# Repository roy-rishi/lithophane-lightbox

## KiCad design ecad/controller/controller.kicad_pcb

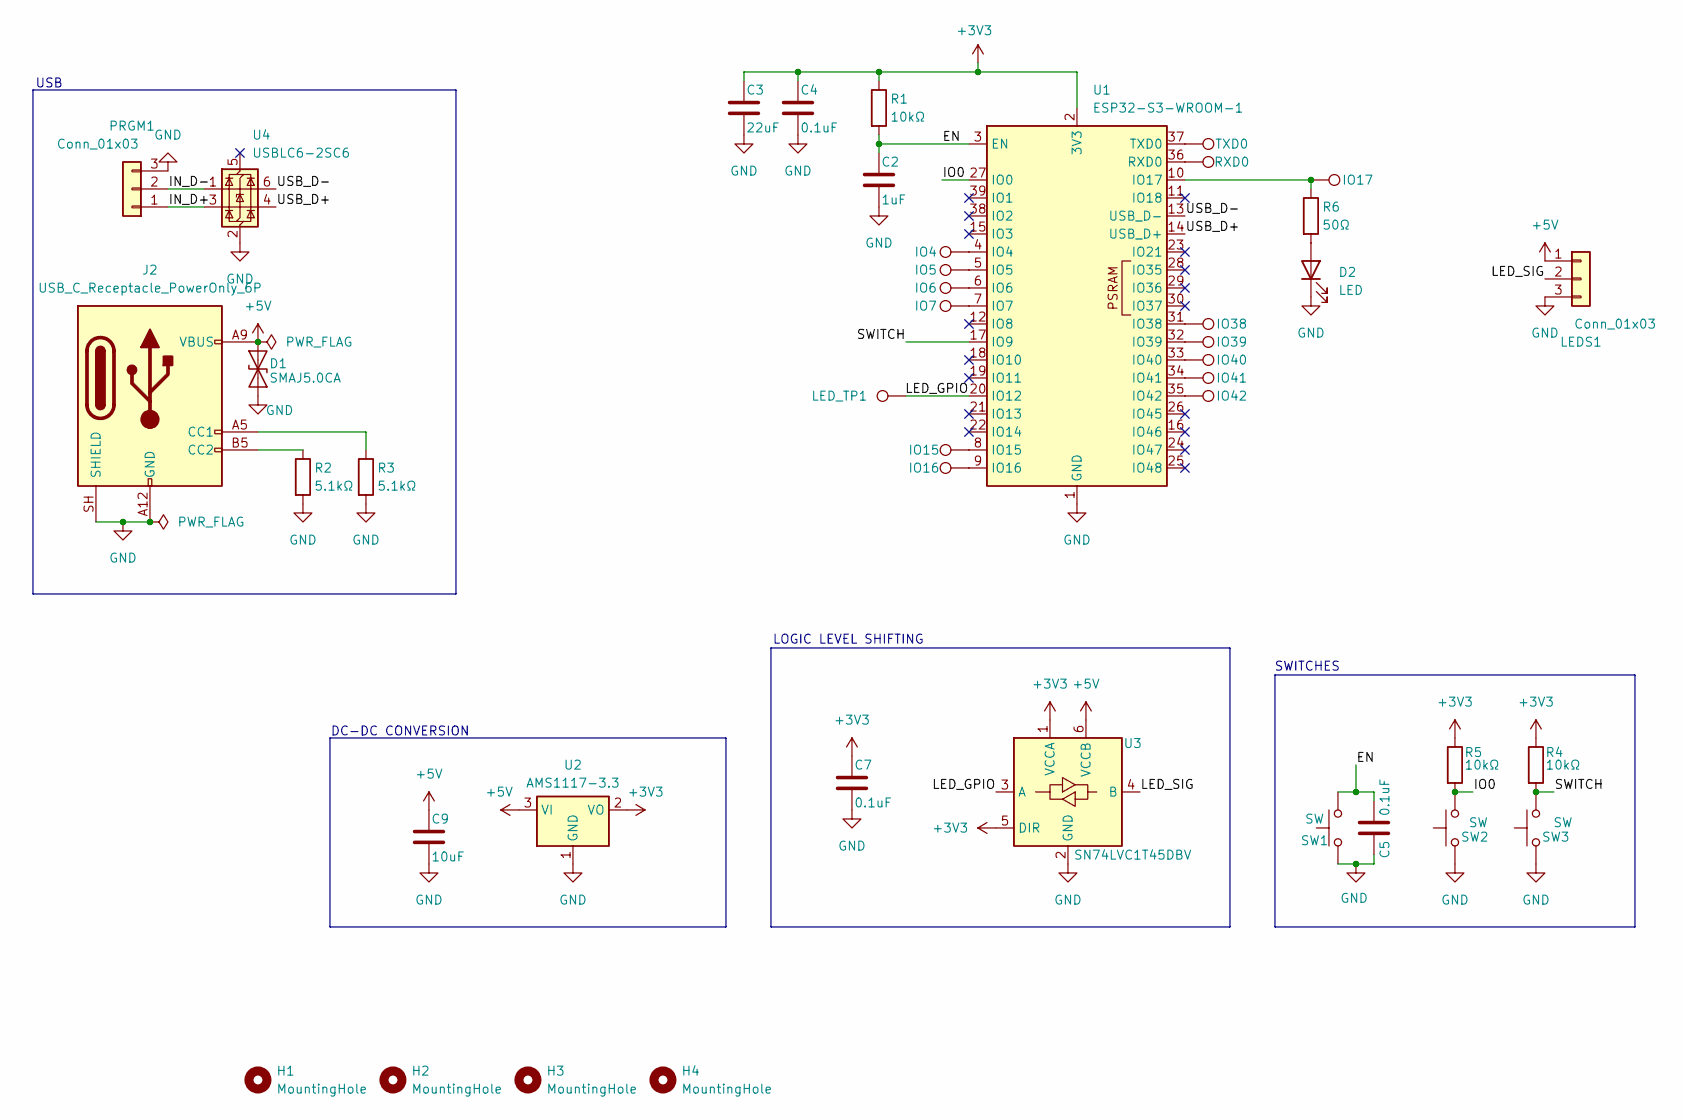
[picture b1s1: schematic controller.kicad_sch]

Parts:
C2: 1uF; C_0805_2012Metric; MPN CL21B105KBFNNNE; LCSC# C28323
C3: 22uF; C_0805_2012Metric; MPN GRM21BR61E226ME44L; LCSC# C86816
C4, C5, C7: 0.1uF; C_0805_2012Metric; MPN CL21B104KBCNNNC; LCSC# C1711
C9: 10uF; C_0805_2012Metric; MPN CL21A106KAYNNNE; LCSC# C15850
D1: SMAJ5.0CA; D_SMA; MPN SMAJ5.0CA; LCSC# C83324
D2: LED; LED_0805_2012Metric_Pad1.15x1.40mm_HandSolder; MPN XL-2012SURC; LCSC# C965812
H1, H2, H3, H4: MountingHole; MountingHole_3.2mm_M3_DIN965_Pad_TopOnly
IO4, IO5, IO6, IO7, IO15, IO16, IO17, IO38, IO39, IO40, IO41, IO42: TestPoint; TestPoint_Pad_D1.5mm
J2: USB_C_Receptacle_PowerOnly_6P; usb-c-vertical-smd; MPN TYPE-C 6PLTH6.8-DJ; LCSC# C5156600
LEDS1: Conn_01x03; JST_XH_B3B-XH-AM_1x03_P2.50mm_Vertical; MPN B3B-XH-A(LF)(SN); LCSC# C144394
LED_TP1: TestPoint; TestPoint_Pad_D1.5mm
PRGM1: Conn_01x03; PinHeader_1x03_P2.54mm_Vertical; MPN HX PH254-01-03-Z-L11.5 pcb pin header; LCSC# C52016391
R1, R4, R5: 10kΩ; R_0805_2012Metric; MPN FRC0805F1002TS; LCSC# C2907219
R2, R3: 5.1kΩ; R_0805_2012Metric; MPN RC0805FR-075K1L; LCSC# C84375
R6: 50Ω; R_0805_2012Metric; MPN ARG05FTC0500; LCSC# C2828866
RXD0: TestPoint; TestPoint_Pad_D1.5mm
SW1, SW2, SW3: SW; SW_SPST_TS-1088-xR020; MPN TS-1088-AR02016; LCSC# C720477
TXD0: TestPoint; TestPoint_Pad_D1.5mm
U1: ESP32-S3-WROOM-1; MPN ESP32-S3-WROOM-1-N16R8; LCSC# C2913202
U2: AMS1117-3.3; SOT-223-3_TabPin2; MPN AMS1117-3.3; LCSC# C6186
U3: SN74LVC1T45DBV; SOT-23-6_Handsoldering; MPN SN74LVC1T45DBVR; LCSC# C7843
U4: USBLC6-2SC6; SOT-23-6_Handsoldering; MPN USBLC6-2SC6; LCSC# C7519

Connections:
+3V3: C3.1, C4.1, C7.1, R1.1, R4.1, R5.1, U1.2 (3V3), U2.2 (VO), U3.1 (VCCA), U3.5 (DIR)
+5V: C9.1, D1.2 (A2), J2.A9 (VBUS), J2.B9 (VBUS), LEDS1.1, U2.3 (VI), U3.6 (VCCB)
/EN: C2.1, C5.1, R1.2, SW1.2, U1.3 (EN)
/IN_D+: PRGM1.1, U4.3 (I/O2)
/IN_D-: PRGM1.2, U4.1 (I/O1)
/IO0: R5.2, SW2.2, U1.27 (IO0)
/LED_GPIO: LED_TP1.1 (1_1), U1.20 (IO12), U3.3 (A)
/LED_SIG: LEDS1.2, U3.4 (B)
/SWITCH: R4.2, SW3.2, U1.17 (IO9)
/USB_D+: U1.14 (USB_D+), U4.4 (I/O2)
/USB_D-: U1.13 (USB_D-), U4.6 (I/O1)
GND: C2.2, C3.2, C4.2, C5.2, C7.2, C9.2, D1.1 (A1), D2.1 (K), J2.A12 (GND), J2.B12 (GND), J2.SH (SHIELD), LEDS1.3, PRGM1.3, R2.2, R3.2, SW1.1, SW2.1, SW3.1, U1.1 (GND), U1.40 (GND), U1.41 (GND), U2.1 (GND), U3.2 (GND), U4.2 (GND)
unnamed: D2.2 (A), R6.2
unnamed: J2.A5 (CC1), R3.1
unnamed: J2.B5 (CC2), R2.1
unnamed: IO4.1 (1_1), U1.4 (IO4)
unnamed: IO5.1 (1_1), U1.5 (IO5)
unnamed: IO6.1 (1_1), U1.6 (IO6)
unnamed: IO7.1 (1_1), U1.7 (IO7)
unnamed: IO15.1 (1_1), U1.8 (IO15)
unnamed: IO16.1 (1_1), U1.9 (IO16)
unnamed: IO17.1 (1_1), R6.1, U1.10 (IO17)
unnamed: IO38.1 (1_1), U1.31 (IO38)
unnamed: IO39.1 (1_1), U1.32 (IO39)
unnamed: IO40.1 (1_1), U1.33 (IO40)
unnamed: IO41.1 (1_1), U1.34 (IO41)
unnamed: IO42.1 (1_1), U1.35 (IO42)
unnamed: RXD0.1 (1_1), U1.36 (RXD0)
unnamed: TXD0.1 (1_1), U1.37 (TXD0)

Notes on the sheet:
SWITCHES
DC-DC CONVERSION
USB
LOGIC LEVEL SHIFTING

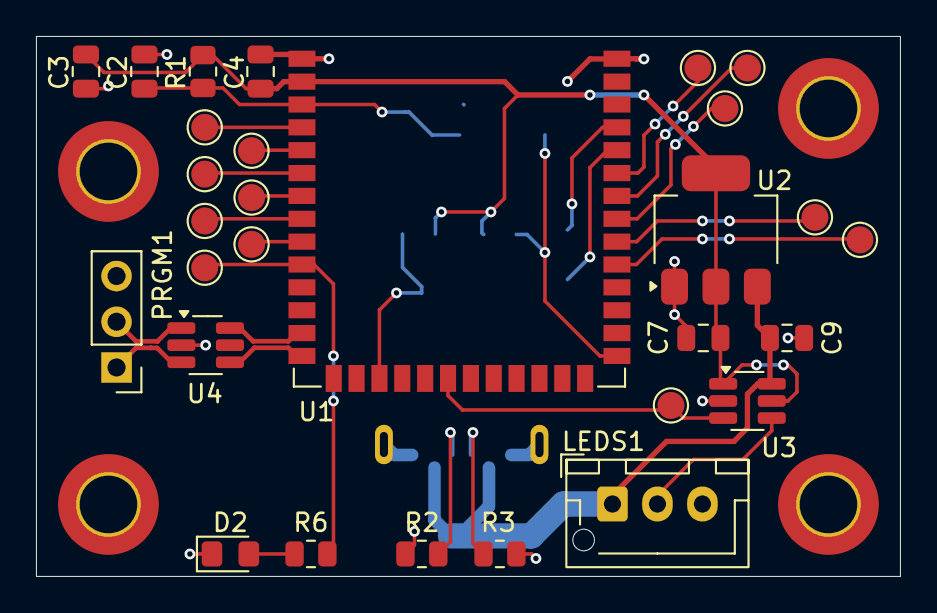
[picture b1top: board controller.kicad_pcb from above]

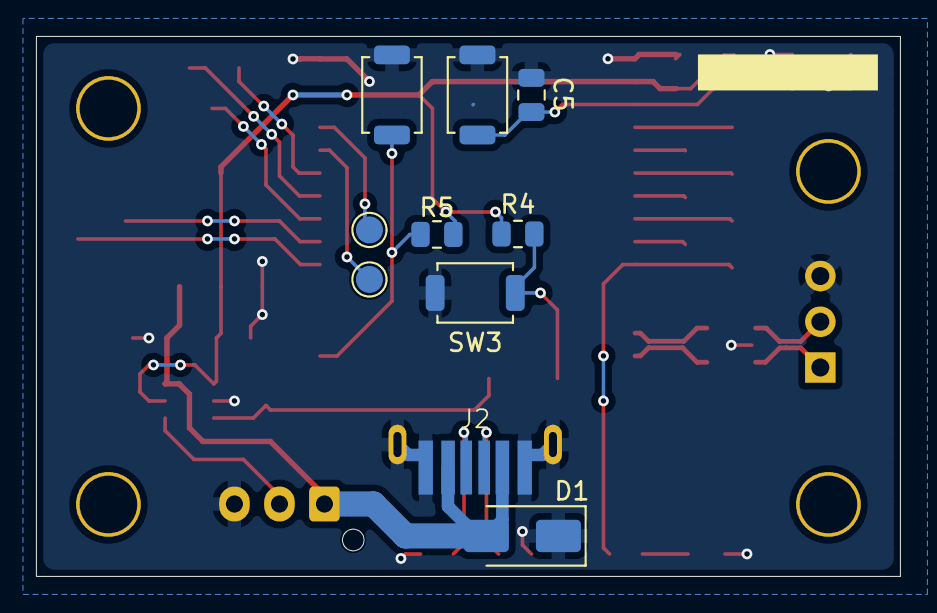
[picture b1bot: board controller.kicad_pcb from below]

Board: 2 copper layers, 48.0 x 30.0 mm, 43 parts (10 on the bottom side), 29 nets.

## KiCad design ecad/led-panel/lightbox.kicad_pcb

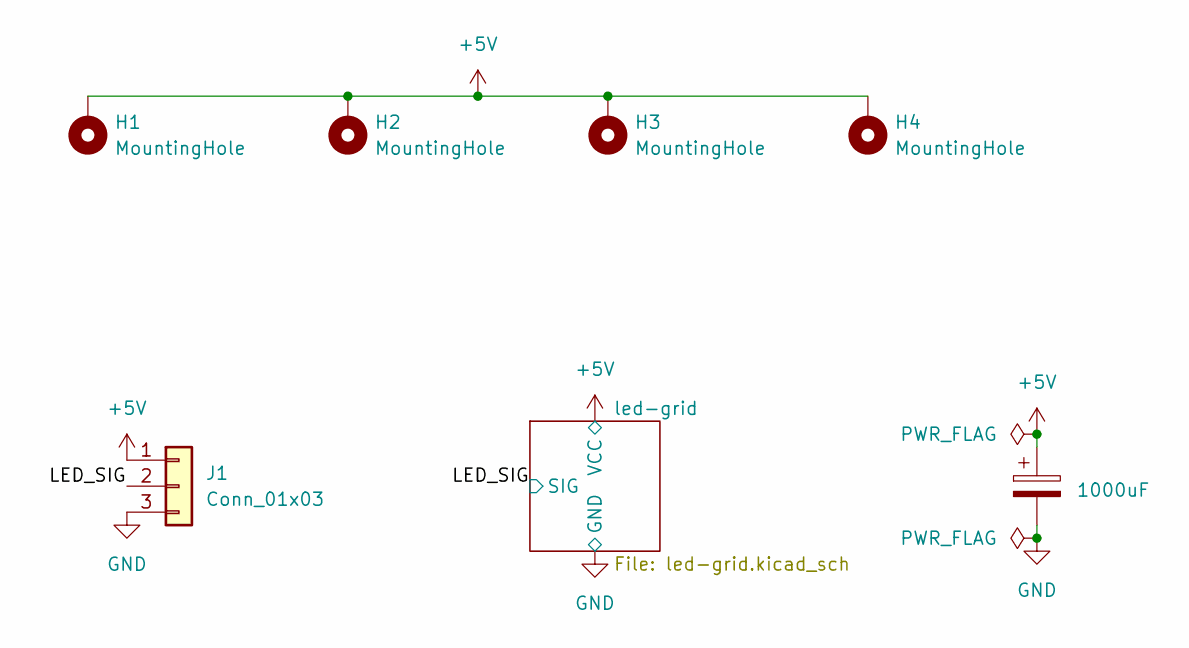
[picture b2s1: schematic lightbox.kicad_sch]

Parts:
C1: 1000uF; C_Elec_10x10.2; MPN RVT1C102M1010; LCSC# C72470
H1, H2, H3, H4: MountingHole; MountingHole_4.3mm_M4_ISO7380_Pad_TopOnly
J1: Conn_01x03; JST_XH_B3B-XH-AM_1x03_P2.50mm_Vertical; MPN B3B-XH-A(LF)(SN); LCSC# C144394

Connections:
+5V: C1.1, H1.1 (1_1), H2.1 (1_1), H3.1 (1_1), H4.1 (1_1), J1.1; also elsewhere on the board
/LED_SIG: J1.2; also elsewhere on the board
GND: C1.2, J1.3; also elsewhere on the board

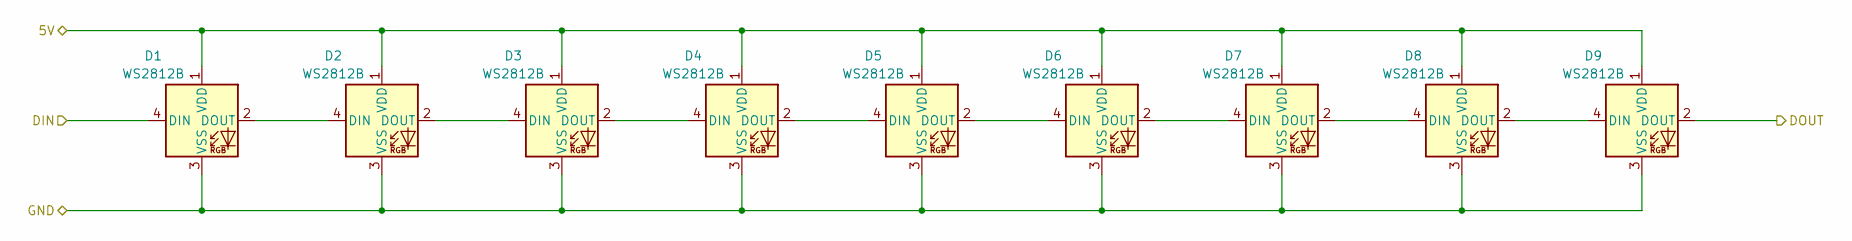
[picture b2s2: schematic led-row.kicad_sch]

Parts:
D1, D2, D3, D4, D5, D6, D7, D8, D9: WS2812B; LED_WS2812B_PLCC4_5.0x5.0mm_P3.2mm; MPN WS2812B-V5/W; LCSC# C2874885

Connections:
+5V: D1.1 (VDD), D2.1 (VDD), D3.1 (VDD), D4.1 (VDD), D5.1 (VDD), D6.1 (VDD), D7.1 (VDD), D8.1 (VDD), D9.1 (VDD); also elsewhere on the board
/LED_SIG: D1.4 (DIN); also elsewhere on the board
/led-grid/led-row/DOUT: D9.2 (DOUT); also elsewhere on the board
GND: D1.3 (VSS), D2.3 (VSS), D3.3 (VSS), D4.3 (VSS), D5.3 (VSS), D6.3 (VSS), D7.3 (VSS), D8.3 (VSS), D9.3 (VSS); also elsewhere on the board
unnamed: D1.2 (DOUT), D2.4 (DIN)
unnamed: D2.2 (DOUT), D3.4 (DIN)
unnamed: D3.2 (DOUT), D4.4 (DIN)
unnamed: D4.2 (DOUT), D5.4 (DIN)
unnamed: D5.2 (DOUT), D6.4 (DIN)
unnamed: D6.2 (DOUT), D7.4 (DIN)
unnamed: D7.2 (DOUT), D8.4 (DIN)
unnamed: D8.2 (DOUT), D9.4 (DIN)

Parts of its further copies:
D10, D11, D12, D13, D14, D15, D16, D17, D18, D19, D20, D21, D22, D23, D24, D25, D26, D27, D28, D29, D30, D31, D32, D33, D34, D35, D36, D37, D38, D39, D40, D41, D42, D43, D44, D45, D46, D47, D48, D49, D50, D51, D52, D53, D54: WS2812B; LED_WS2812B_PLCC4_5.0x5.0mm_P3.2mm; MPN WS2812B-V5/W; LCSC# C2874885

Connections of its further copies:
+5V: D10.1 (VDD), D11.1 (VDD), D12.1 (VDD), D13.1 (VDD), D14.1 (VDD), D15.1 (VDD), D16.1 (VDD), D17.1 (VDD), D18.1 (VDD), D19.1 (VDD), D20.1 (VDD), D21.1 (VDD), D22.1 (VDD), D23.1 (VDD), D24.1 (VDD), D25.1 (VDD), D26.1 (VDD), D27.1 (VDD), D28.1 (VDD), D29.1 (VDD), D30.1 (VDD), D31.1 (VDD), D32.1 (VDD), D33.1 (VDD), D34.1 (VDD), D35.1 (VDD), D36.1 (VDD), D37.1 (VDD), D38.1 (VDD), D39.1 (VDD), D40.1 (VDD), D41.1 (VDD), D42.1 (VDD), D43.1 (VDD), D44.1 (VDD), D45.1 (VDD), D46.1 (VDD), D47.1 (VDD), D48.1 (VDD), D49.1 (VDD), D50.1 (VDD), D51.1 (VDD), D52.1 (VDD), D53.1 (VDD), D54.1 (VDD); also elsewhere on the board
/led-grid/led-row1/DOUT: D18.2 (DOUT), D19.4 (DIN)
/led-grid/led-row2/DOUT: D27.2 (DOUT), D28.4 (DIN)
/led-grid/led-row3/DOUT: D36.2 (DOUT), D37.4 (DIN)
/led-grid/led-row4/DOUT: D45.2 (DOUT), D46.4 (DIN)
/led-grid/led-row5/DOUT: D54.2 (DOUT)
/led-grid/led-row/DOUT: D10.4 (DIN); also elsewhere on the board
GND: D10.3 (VSS), D11.3 (VSS), D12.3 (VSS), D13.3 (VSS), D14.3 (VSS), D15.3 (VSS), D16.3 (VSS), D17.3 (VSS), D18.3 (VSS), D19.3 (VSS), D20.3 (VSS), D21.3 (VSS), D22.3 (VSS), D23.3 (VSS), D24.3 (VSS), D25.3 (VSS), D26.3 (VSS), D27.3 (VSS), D28.3 (VSS), D29.3 (VSS), D30.3 (VSS), D31.3 (VSS), D32.3 (VSS), D33.3 (VSS), D34.3 (VSS), D35.3 (VSS), D36.3 (VSS), D37.3 (VSS), D38.3 (VSS), D39.3 (VSS), D40.3 (VSS), D41.3 (VSS), D42.3 (VSS), D43.3 (VSS), D44.3 (VSS), D45.3 (VSS), D46.3 (VSS), D47.3 (VSS), D48.3 (VSS), D49.3 (VSS), D50.3 (VSS), D51.3 (VSS), D52.3 (VSS), D53.3 (VSS), D54.3 (VSS); also elsewhere on the board
unnamed: D10.2 (DOUT), D11.4 (DIN)
unnamed: D11.2 (DOUT), D12.4 (DIN)
unnamed: D12.2 (DOUT), D13.4 (DIN)
unnamed: D13.2 (DOUT), D14.4 (DIN)
unnamed: D14.2 (DOUT), D15.4 (DIN)
unnamed: D15.2 (DOUT), D16.4 (DIN)
unnamed: D16.2 (DOUT), D17.4 (DIN)
unnamed: D17.2 (DOUT), D18.4 (DIN)
unnamed: D19.2 (DOUT), D20.4 (DIN)
unnamed: D20.2 (DOUT), D21.4 (DIN)
unnamed: D21.2 (DOUT), D22.4 (DIN)
unnamed: D22.2 (DOUT), D23.4 (DIN)
unnamed: D23.2 (DOUT), D24.4 (DIN)
unnamed: D24.2 (DOUT), D25.4 (DIN)
unnamed: D25.2 (DOUT), D26.4 (DIN)
unnamed: D26.2 (DOUT), D27.4 (DIN)
unnamed: D28.2 (DOUT), D29.4 (DIN)
unnamed: D29.2 (DOUT), D30.4 (DIN)
unnamed: D30.2 (DOUT), D31.4 (DIN)
unnamed: D31.2 (DOUT), D32.4 (DIN)
unnamed: D32.2 (DOUT), D33.4 (DIN)
unnamed: D33.2 (DOUT), D34.4 (DIN)
unnamed: D34.2 (DOUT), D35.4 (DIN)
unnamed: D35.2 (DOUT), D36.4 (DIN)
unnamed: D37.2 (DOUT), D38.4 (DIN)
unnamed: D38.2 (DOUT), D39.4 (DIN)
unnamed: D39.2 (DOUT), D40.4 (DIN)
unnamed: D40.2 (DOUT), D41.4 (DIN)
unnamed: D41.2 (DOUT), D42.4 (DIN)
unnamed: D42.2 (DOUT), D43.4 (DIN)
unnamed: D43.2 (DOUT), D44.4 (DIN)
unnamed: D44.2 (DOUT), D45.4 (DIN)
unnamed: D46.2 (DOUT), D47.4 (DIN)
unnamed: D47.2 (DOUT), D48.4 (DIN)
unnamed: D48.2 (DOUT), D49.4 (DIN)
unnamed: D49.2 (DOUT), D50.4 (DIN)
unnamed: D50.2 (DOUT), D51.4 (DIN)
unnamed: D51.2 (DOUT), D52.4 (DIN)
unnamed: D52.2 (DOUT), D53.4 (DIN)
unnamed: D53.2 (DOUT), D54.4 (DIN)

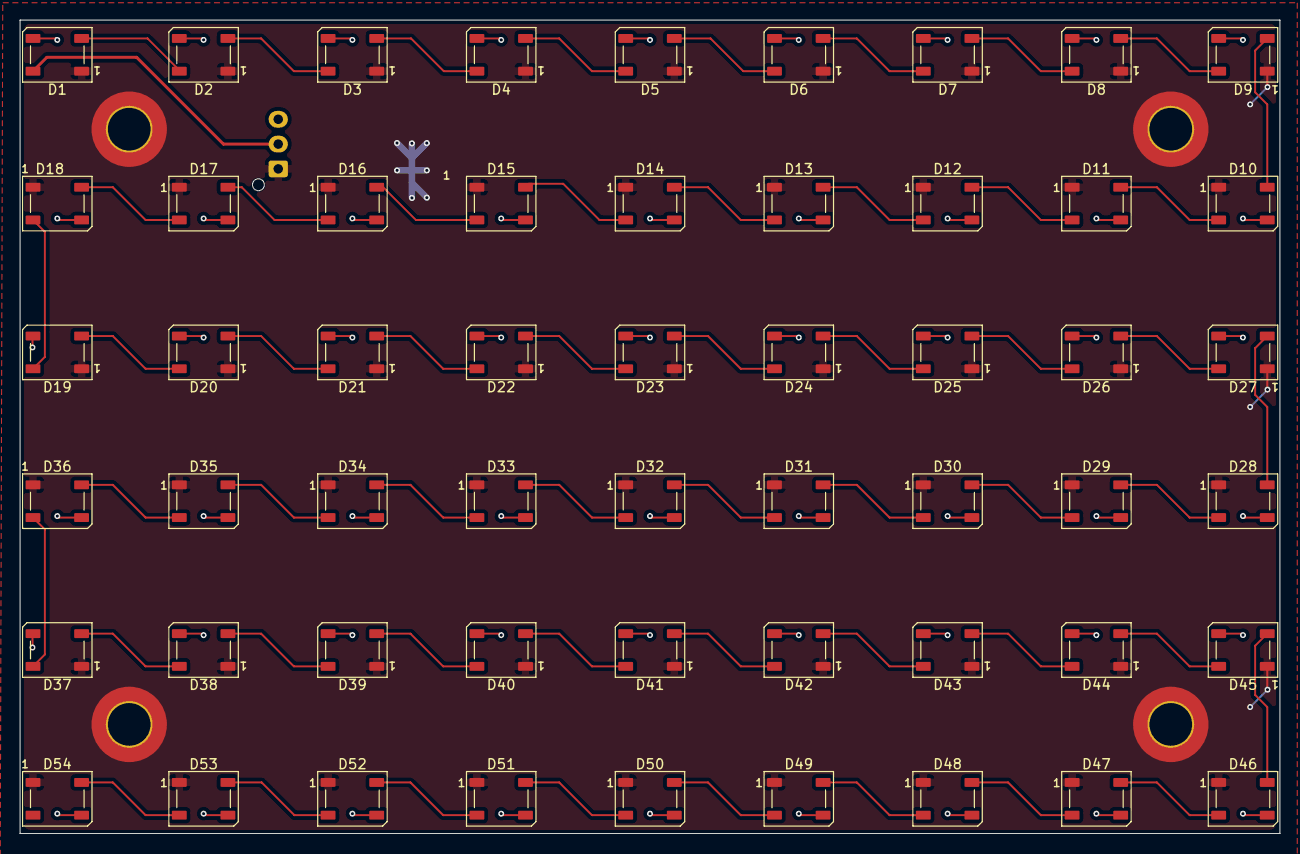
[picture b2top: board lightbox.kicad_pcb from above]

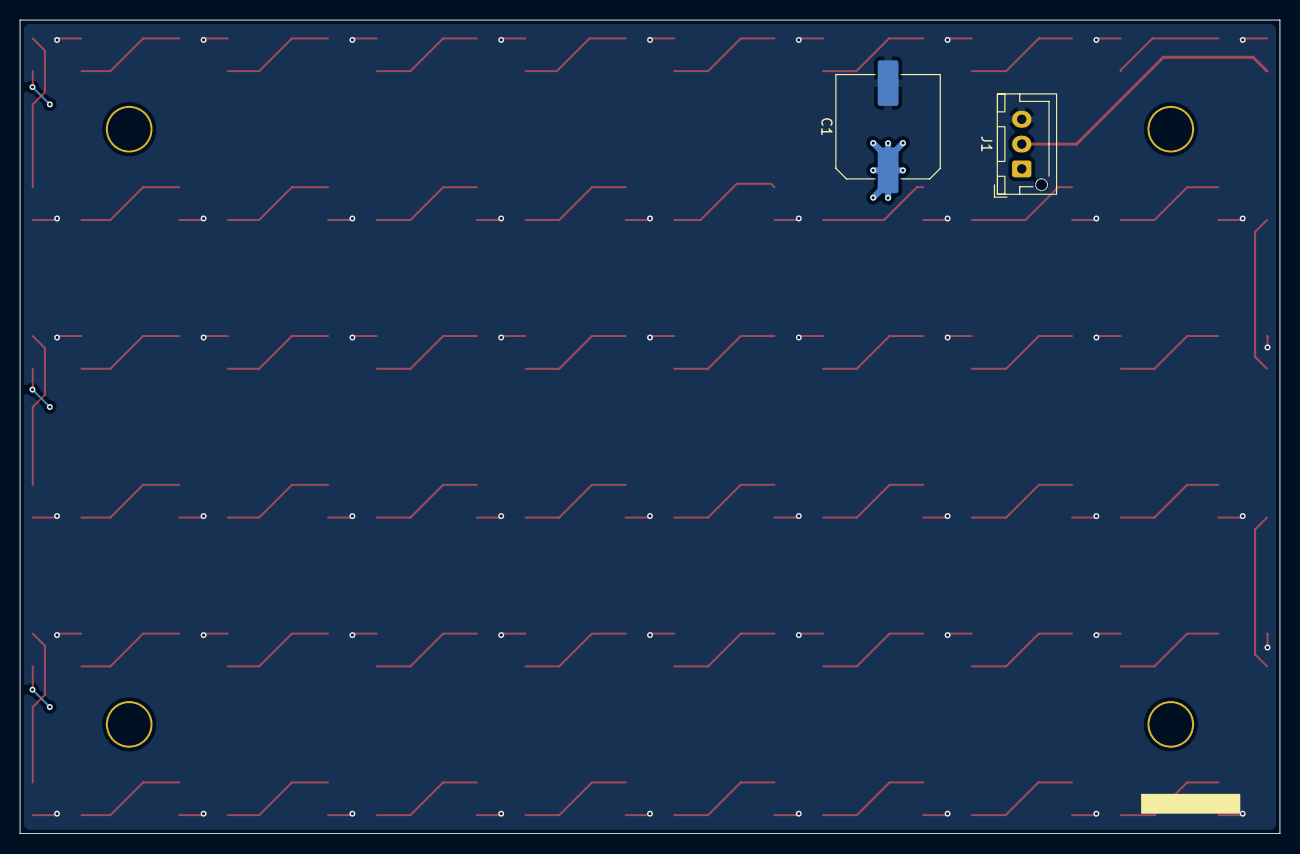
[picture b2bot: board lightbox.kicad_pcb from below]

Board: 2 copper layers, 127.0 x 82.0 mm, 60 parts (2 on the bottom side), 56 nets.

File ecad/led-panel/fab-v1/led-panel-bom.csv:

"Reference","Quantity","Value","Exclude from BOM","Footprint","Manufacture Part Number","LCSC Part Number"
"D1,D2,D3,D4,D5,D6,D7,D8,D9,D10,D11,D12,D13,D14,D15,D16,D17,D18,D19,D20,D21,D22,D23,D24,D25,D26,D27,D28,D29,D30,D31,D32,D33,D34,D35,D36,D37,D38,D39,D40,D41,D42,D43,D44,D45,D46,D47,D48,D49,D50,D51,D52,D53,D54","54","WS2812B","","LED_SMD:LED_WS2812B_PLCC4_5.0x5.0mm_P3.2mm","WS2812B-V5/W","C2874885"
"J1","1","Conn_01x03","","Connector_JST:JST_XH_B3B-XH-AM_1x03_P2.50mm_Vertical","B3B-XH-A(LF)(SN)","C144394"
"C1","1","1000uF","","Capacitor_SMD:C_Elec_10x10.2","RVT1C102M1010","C72470"
